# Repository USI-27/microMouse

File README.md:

# MicroMouse  Project

This project implements a micromouse robot using a Raspberry Pi Pico W microcontroller. The robot is designed to solve a maze using the flood fill algorithm, with advanced motion control, wall detection, and a custom-designed PCB.

## Repository Structure

```
MicroMouse/
├── MicroMouse Software/       # Firmware source code
│   ├── Headers/                # Header files (.h)
│   ├── images/                 # README images
│   ├── Cell.cpp
│   ├── IR_Sensors.cpp
│   ├── Int_Vector.cpp
│   ├── Maze_Algorithm.cpp
│   ├── Motion_Planner.cpp
│   ├── Profile.cpp
│   ├── Queue.cpp
│   └── Simple_Run_Micromouse_V1.ino
└── MicroMouse Design Files/   # Hardware design files
    ├── mm3.0/                  # KiCad project (schematic + PCB)
    ├── manufacturing/          # Gerbers, drill files, BOM, pick-and-place
    ├── images/                 # PCB and assembly renders
    ├── schematic.pdf
    └── HARDWARE.md             # Detailed hardware documentation
```

## Hardware Implementation

The image above shows the actual hardware implementation of the micromouse robot, featuring:

- Raspberry Pi Pico W at the center
- Dual motor setup with encoders
- IR sensors for wall detection
- Custom PCB design for component integration
- Compact and efficient layout

Full PCB schematics, KiCad source files, manufacturing (Gerber/BOM) files, and design writeups are available in [`MicroMouse Design Files/`](MicroMouse%20Design%20Files/) — see [`HARDWARE.md`](MicroMouse%20Design%20Files/HARDWARE.md) for a detailed breakdown of the sensor placement and board layout.

## Achievements 🏆

- 🥇 **1st Place** at IIT Roorkee's Annual Tech Fest - Cognizance '25, Micromouse Competition (Prize: ₹1,00,000)
- 🥇 **1st Place** at Delhi Technological University's Annual Tech Fest - Invictus '25, Micromouse Competition
- 🥇 **1st Place** at BITS Pilani's Annual Tech Fest - Apogee '25, Micromouse Competition
- 🥉 **3rd Place** at IIT Jodhpur's Annual Tech Fest - Prometeo '25, Micromouse Competition
- 🥉 **3rd Place** at RGIPT's Annual Tech Fest - Urjotsav '24

## Video Demonstration

Check out the micromouse robot in action: [Watch on YouTube](https://www.youtube.com/watch?v=1PZht_hqyYY)

## Hardware Components

- **Microcontroller**: Raspberry Pi Pico W
- **Motors**: 2 DC motors with encoders
- **Sensors**:
  - IR sensors for wall detection (Left, Right, Front)
  - MPU6050 gyroscope for orientation
  - Encoders for distance measurement
- **Motor Driver**: TB6612FNG dual motor driver

## Project Structure (Software)

The firmware is organized into several key components:

1. **Cell.h/cpp** — Defines the maze cell structure and properties
2. **Int_Vector.h/cpp** — Custom vector implementation for sensor data
3. **IR_Sensors.h/cpp** — Wall detection and sensor reading functionality
4. **Maze_Algorithm.h/cpp** — Flood fill algorithm and maze solving logic
5. **Motion_Planner.h/cpp** — Movement control and motor functions
6. **Profile.h/cpp** — Global configuration and pin definitions
7. **Queue.h/cpp** — Queue implementation for flood fill algorithm

## How It Works

### 1. Initialization (`setup()`)

- Configures serial communication
- Initializes MPU6050 gyroscope
- Sets up encoder pins and interrupts
- Configures motor driver pins
- Sets initial maze walls for the starting position

### 2. Maze Exploration Flow

The robot explores the maze in multiple rounds:

```cpp
for (int round = 1; round <= Exploration_Rounds; round++) {
    searchMode = FIND_CENTRE;  // First find the center
    findGoal();
    searchMode = FIND_START;   // Then return to start
    findGoal();
}
```

### 3. Flood Fill Algorithm

The flood fill algorithm works as follows:

1. Initializes all cells with -1 cost
2. Sets goal cells (center or start) with cost 0
3. Propagates costs to neighboring cells
4. Robot moves to the neighboring cell with lowest cost

### 4. Wall Detection

- Uses IR sensors to detect walls
- Updates maze wall information in real-time
- Maintains wall consistency between adjacent cells

### 5. Movement Control

The robot uses several movement functions:

- `moveForward()`: Move one cell forward
- `turnLeft()`: Turn 90 degrees left
- `turnRight()`: Turn 90 degrees right
- Uses PD (Proportional-Derivative) control for smooth motion
- Gyroscope feedback for accurate turns
- Encoder feedback for distance measurement

### 6. Navigation Logic

**Wall Update:**
```cpp
updateWalls();  // Detect and update wall information
```

**Path Planning:**
```cpp
floodOpenNeighbours();     // Update cell costs
getMinDistanceDirection();  // Choose best direction
```

**Movement:**
```cpp
moveInDirection();  // Execute movement
```

## Key Features

**Adaptive Movement:**
- PD control for straight line motion
- Gyroscope-based rotation control
- Wall following capability

**Intelligent Maze Solving:**
- Flood fill algorithm for path planning
- Multiple exploration rounds
- Efficient center finding and return to start

**Robust Sensor Integration:**
- IR sensor filtering
- Encoder-based distance measurement
- Gyroscope-based orientation tracking

## Configuration

Key parameters can be adjusted in `Profile.h`:

- `MAZE_SIZE`: Size of the maze (default: 8x8)
- `Exploration_Rounds`: Number of exploration rounds
- Sensor thresholds
- Motor control parameters

## Usage

1. Upload the code (`Simple_Run_Micromouse_V1.ino`) to the Raspberry Pi Pico W
2. Place the robot at the start position (0,0)
3. The robot will automatically:
   - Find the path to the center
   - Return to start
   - Repeat for the specified number of rounds
   - Make a final run to the center

## Debugging

- LED indicators for status
- Serial output for debugging
- Button to clear maze walls

## Authors

Built by [USI-27](https://github.com/USI-27) and [paramveer5404](https://github.com/paramveer5404) .

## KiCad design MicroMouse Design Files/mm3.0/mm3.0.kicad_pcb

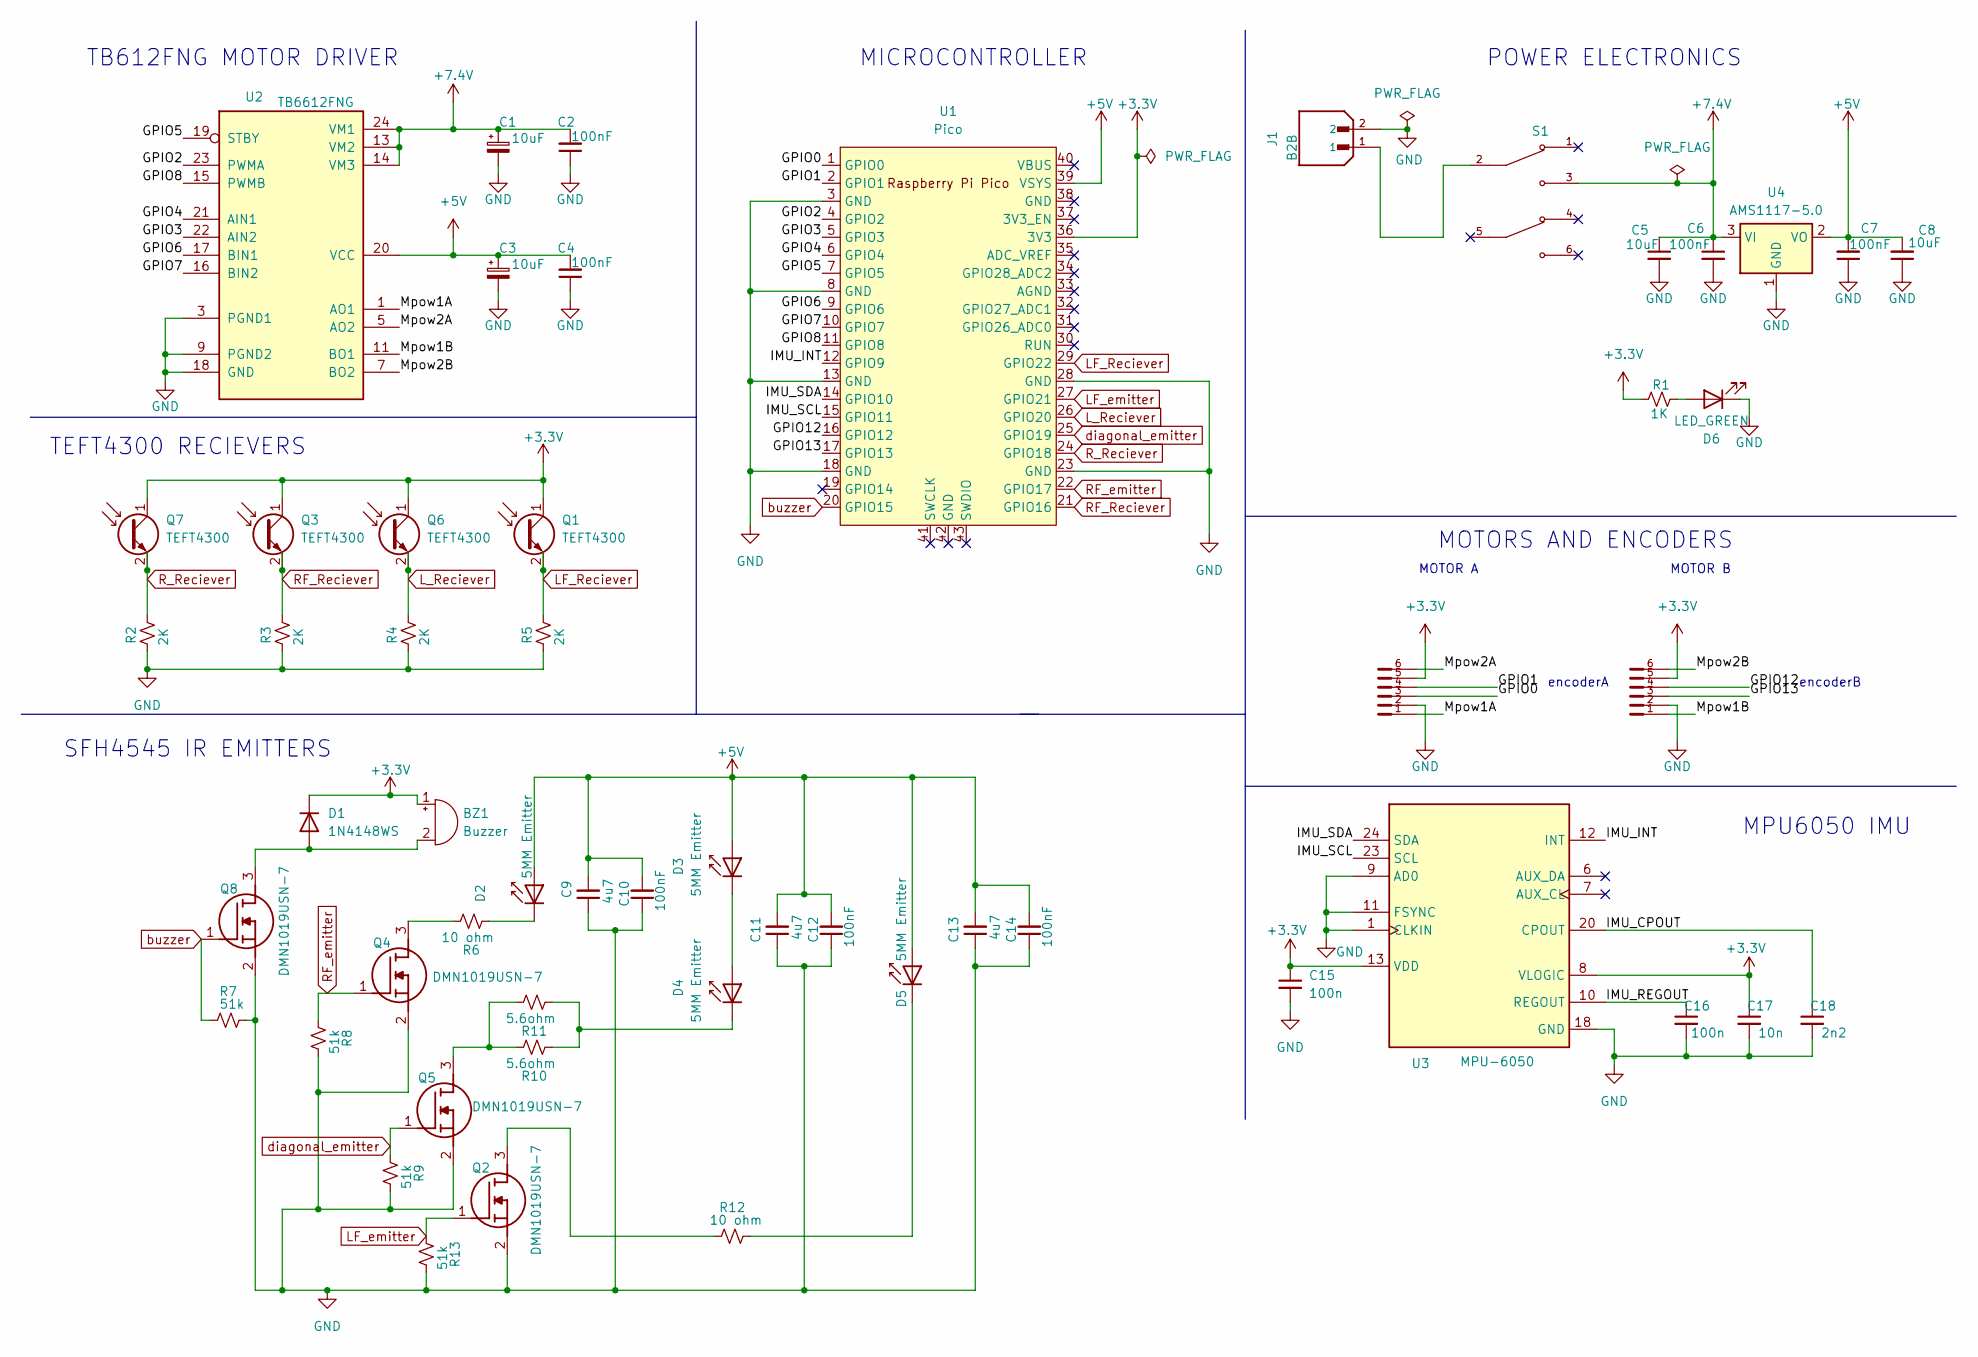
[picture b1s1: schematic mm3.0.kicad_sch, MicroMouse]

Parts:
BZ1: Buzzer; Buzzer_12x9.5RM7.6
C1, C3: 10uF; CP_EIA-3216-10_Kemet-I_Pad1.58x1.35mm_HandSolder; LCSC C7171
C2, C4, C10, C12, C14: 100nF; C_0402_1005Metric_Pad0.74x0.62mm_HandSolder; LCSC C307331
C5, C8: 10uF; C_0805_2012Metric_Pad1.18x1.45mm_HandSolder; LCSC C440198
C6, C7: 100nF; C_0805_2012Metric_Pad1.18x1.45mm_HandSolder; LCSC C495959
C9, C11: 4u7; C_0805_2012Metric_Pad1.18x1.45mm_HandSolder; LCSC C1779
C13: 4u7; C_0805_2012Metric_Pad1.18x1.45mm_HandSolder
C15: 100n; C_0402_1005Metric_Pad0.74x0.62mm_HandSolder; LCSC C307331
C16: 100n; C_0805_2012Metric_Pad1.18x1.45mm_HandSolder; LCSC C495959
C17: 10n; C_0805_2012Metric_Pad1.18x1.45mm_HandSolder; LCSC C1710
C18: 2n2; C_0805_2012Metric_Pad1.18x1.45mm_HandSolder; LCSC C28260
D1: 1N4148WS; D_SOD-323_HandSoldering; LCSC C2128
D2, D3, D4, D5: 5MM Emitter; LED_D5.0mm_IRBlack
D6: LED_GREEN; LED_0805_2012Metric_Pad1.15x1.40mm_HandSolder; LCSC C2297
J1: B2B; JST_XH_B2B-XH-AM_1x02_P2.50mm_Vertical; PARTREV N/A; LCSC C158012
Q1, Q3, Q6, Q7: TEFT4300; LED_D3.0mm_Clear; LCSC C118301
Q2, Q4, Q5, Q8: DMN1019USN-7; SOT95P285X140-3N; Manufacturer_Part_Number DMN1019USN-7; LCSC C145103
R1: 1K; R_0402_1005Metric_Pad0.72x0.64mm_HandSolder; LCSC C11702
R2, R3, R4, R5: 2K; R_1206_3216Metric_Pad1.30x1.75mm_HandSolder; LCSC C17944
R6, R12: 10 ohm; R_0805_2012Metric_Pad1.20x1.40mm_HandSolder; LCSC C136903
R7, R8, R9, R13: 51k; R_2010_5025Metric_Pad1.40x2.65mm_HandSolder; LCSC C20435
R10, R11: 5.6ohm; R_0402_1005Metric_Pad0.72x0.64mm_HandSolder; LCSC C25175
S1: SW_TL2230EEF140; PARTREV E
U1: Pico; RPi_Pico_SMD_TH; LCSC C7203003
U2: TB6612FNG; SSOP-24_5.3x8.2mm_P0.65mm; LCSC C141517
U3: MPU-6050; InvenSense_QFN-24_4x4mm_P0.5mm; LCSC C24112
U4: AMS1117-5.0; SOT-223-3_TabPin2; LCSC C6187
X1, X2: B6B-ZR; DigiKey_Part_Number 455-B6B-ZR-ND

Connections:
+3.3V: BZ1.1 (+), C15.1, C17.1, D1.1 (K), Q1.1 (C), Q3.1 (C), Q6.1 (C), Q7.1 (C), R1.1, U1.36 (3V3), U3.8 (VLOGIC), U3.13 (VDD), X1.5, X2.5
+5V: C3.1, C4.2, C7.2, C8.2, C9.2, C10.2, C11.2, C12.2, C13.2, C14.2, D2.2 (A), D3.2 (A), D5.2 (A), U1.39 (VSYS), U2.20 (VCC), U4.2 (VO)
+7.4V: C1.1, C2.2, C5.1, C6.1, S1.3, U2.13 (VM2), U2.14 (VM3), U2.24 (VM1), U4.3 (VI)
/GPIO0: U1.1 (GPIO0), X1.3
/GPIO1: U1.2 (GPIO1), X1.4
/GPIO2: U1.4 (GPIO2), U2.23 (PWMA)
/GPIO3: U1.5 (GPIO3), U2.22 (AIN2)
/GPIO4: U1.6 (GPIO4), U2.21 (AIN1)
/GPIO5: U1.7 (GPIO5), U2.19 (STBY)
/GPIO6: U1.9 (GPIO6), U2.17 (BIN1)
/GPIO7: U1.10 (GPIO7), U2.16 (BIN2)
/GPIO8: U1.11 (GPIO8), U2.15 (PWMB)
/GPIO12: U1.16 (GPIO12), X2.4
/GPIO13: U1.17 (GPIO13), X2.3
/IMU_CPOUT: C18.1, U3.20 (CPOUT)
/IMU_INT: U1.12 (GPIO9), U3.12 (INT)
/IMU_REGOUT: C16.1, U3.10 (REGOUT)
/IMU_SCL: U1.15 (GPIO11), U3.23 (SCL)
/IMU_SDA: U1.14 (GPIO10), U3.24 (SDA)
/Mpow1A: U2.1 (AO1), U2.2 (AO1), X1.1
/Mpow1B: U2.11 (BO1), U2.12 (BO1), X2.1
/Mpow2A: U2.5 (AO2), U2.6 (AO2), X1.6
/Mpow2B: U2.7 (BO2), U2.8 (BO2), X2.6
GND: C1.2, C2.1, C3.2, C4.1, C5.2, C6.2, C7.1, C8.1, C9.1, C10.1, C11.1, C12.1, C13.1, C14.1, C15.2, C16.2, C17.2, C18.2, D6.1 (K), J1.2, Q2.2 (S), Q4.2 (S), Q5.2 (S), Q8.2 (S), R2.2, R3.2, R4.2, R5.2, R7.2, R8.2, R9.2, R13.2, U1.3 (GND), U1.8 (GND), U1.13 (GND), U1.18 (GND), U1.23 (GND), U1.28 (GND), U2.3 (PGND1), U2.4 (PGND1), U2.9 (PGND2), U2.10 (PGND2), U2.18 (GND), U3.1 (CLKIN), U3.9 (AD0), U3.11 (FSYNC), U3.18 (GND), U4.1 (GND), X1.2, X2.2
LF_Reciever: Q1.2 (E), R5.1, U1.29 (GPIO22)
LF_emitter: Q2.1 (G), R13.1, U1.27 (GPIO21)
L_Reciever: Q6.2 (E), R4.1, U1.26 (GPIO20)
unnamed: BZ1.2 (-), D1.2 (A), Q8.3 (D)
unnamed: D2.1 (K), R6.1
unnamed: D3.1 (K), D4.2 (A)
unnamed: D4.1 (K), R10.1, R11.1
unnamed: D5.1 (K), R12.2
unnamed: D6.2 (A), R1.2
unnamed: J1.1, S1.2
unnamed: Q2.3 (D), R12.1
unnamed: Q4.3 (D), R6.2
unnamed: Q5.3 (D), R10.2, R11.2
RF_Reciever: Q3.2 (E), R3.1, U1.21 (GPIO16)
RF_emitter: Q4.1 (G), R8.1, U1.22 (GPIO17)
R_Reciever: Q7.2 (E), R2.1, U1.24 (GPIO18)
buzzer: Q8.1 (G), R7.1, U1.20 (GPIO15)
diagonal_emitter: Q5.1 (G), R9.1, U1.25 (GPIO19)

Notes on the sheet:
encoderA
MOTORS AND ENCODERS
POWER ELECTRONICS
MICROCONTROLLER
TB612FNG MOTOR DRIVER
SFH4545 IR EMITTERS
MOTOR B
TEFT4300 RECIEVERS
MPU6050 IMU
encoderB
MOTOR A

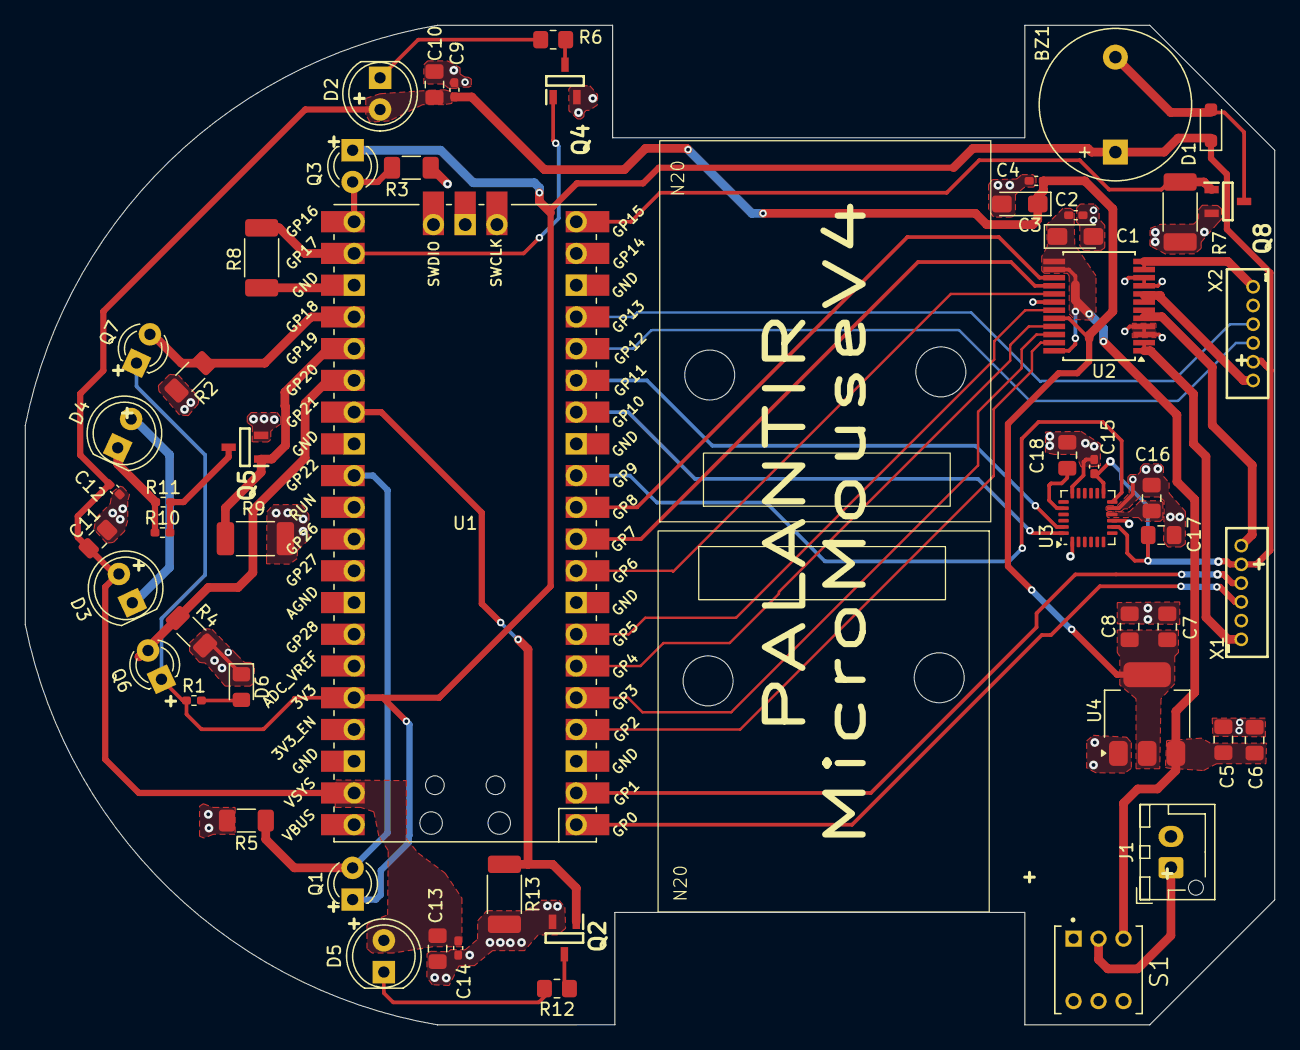
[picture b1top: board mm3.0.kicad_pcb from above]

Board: 2 copper layers, 100.0 x 80.0 mm, 57 parts (1 on the bottom side), 42 nets.

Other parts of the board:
N20, N20#2: N20; N20MotorWithMount
logo: LOGO

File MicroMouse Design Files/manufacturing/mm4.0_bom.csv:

Designator,Comment,Footprint,LCSC
C1,10uF,Capacitor_Tantalum_SMD:CP_EIA-3216-10_Kemet-I_Pad1.58x1.35mm_HandSolder,C7171
C2,100nF,Capacitor_SMD:C_0402_1005Metric_Pad0.74x0.62mm_HandSolder,C307331
C3,10uF,Capacitor_Tantalum_SMD:CP_EIA-3216-10_Kemet-I_Pad1.58x1.35mm_HandSolder,C7171
C4,100nF,Capacitor_SMD:C_0402_1005Metric_Pad0.74x0.62mm_HandSolder,C307331
C5,10uF,Capacitor_SMD:C_0805_2012Metric_Pad1.18x1.45mm_HandSolder,C440198
C6,100nF,Capacitor_SMD:C_0805_2012Metric_Pad1.18x1.45mm_HandSolder,C495959
C7,100nF,Capacitor_SMD:C_0805_2012Metric_Pad1.18x1.45mm_HandSolder,C495959
C8,10uF,Capacitor_SMD:C_0805_2012Metric_Pad1.18x1.45mm_HandSolder,C440198
C9,4u7,Capacitor_SMD:C_0805_2012Metric_Pad1.18x1.45mm_HandSolder,C1779
C10,100nF,Capacitor_SMD:C_0402_1005Metric_Pad0.74x0.62mm_HandSolder,C307331
C11,4u7,Capacitor_SMD:C_0805_2012Metric_Pad1.18x1.45mm_HandSolder,C1779
C12,100nF,Capacitor_SMD:C_0402_1005Metric_Pad0.74x0.62mm_HandSolder,C307331
C13,4u7,Capacitor_SMD:C_0805_2012Metric_Pad1.18x1.45mm_HandSolder,C1779
C14,100nF,Capacitor_SMD:C_0402_1005Metric_Pad0.74x0.62mm_HandSolder,C307331
C15,100n,Capacitor_SMD:C_0402_1005Metric_Pad0.74x0.62mm_HandSolder,C307331
C16,100n,Capacitor_SMD:C_0805_2012Metric_Pad1.18x1.45mm_HandSolder,C495959
C17,10n,Capacitor_SMD:C_0805_2012Metric_Pad1.18x1.45mm_HandSolder,C1710
C18,2n2,Capacitor_SMD:C_0805_2012Metric_Pad1.18x1.45mm_HandSolder,C28260
D1,1N4148WS,Diode_SMD:D_SOD-323_HandSoldering,C2128
D2,5MM Emitter,LED_THT:LED_D5.0mm_IRBlack,
D3,5MM Emitter,LED_THT:LED_D5.0mm_IRBlack,
D4,5MM Emitter,LED_THT:LED_D5.0mm_IRBlack,
D5,5MM Emitter,LED_THT:LED_D5.0mm_IRBlack,
D6,LED_GREEN,LED_SMD:LED_0805_2012Metric_Pad1.15x1.40mm_HandSolder,C2297
J1,B2B,Connector_JST:JST_XH_B2B-XH-AM_1x02_P2.50mm_Vertical,C158012
J2,B2B,Connector_JST:JST_XH_B2B-XH-AM_1x02_P2.50mm_Vertical,C158012
Q1,TEFT4300,LED_THT:LED_D3.0mm_Clear,C118301
Q2,DMN1019USN-7,SPX3819M5-L-5-0:SOT95P285X140-3N,C145103
Q3,TEFT4300,LED_THT:LED_D3.0mm_Clear,C118301
Q4,DMN1019USN-7,SPX3819M5-L-5-0:SOT95P285X140-3N,C145103
Q5,DMN1019USN-7,SPX3819M5-L-5-0:SOT95P285X140-3N,C145103
Q6,TEFT4300,LED_THT:LED_D3.0mm_Clear,C118301
Q7,TEFT4300,LED_THT:LED_D3.0mm_Clear,C118301
Q8,DMN1019USN-7,SPX3819M5-L-5-0:SOT95P285X140-3N,C145103
R1,1K,Resistor_SMD:R_0402_1005Metric_Pad0.72x0.64mm_HandSolder,C11702
R2,2K,Resistor_SMD:R_1206_3216Metric_Pad1.30x1.75mm_HandSolder,C17944
R3,2K,Resistor_SMD:R_1206_3216Metric_Pad1.30x1.75mm_HandSolder,C17944
R4,2K,Resistor_SMD:R_1206_3216Metric_Pad1.30x1.75mm_HandSolder,C17944
R5,2K,Resistor_SMD:R_1206_3216Metric_Pad1.30x1.75mm_HandSolder,C17944
R6,10 ohm,Resistor_SMD:R_0805_2012Metric_Pad1.20x1.40mm_HandSolder,C136903
R7,51k,Resistor_SMD:R_2010_5025Metric_Pad1.40x2.65mm_HandSolder,C20435
R8,51k,Resistor_SMD:R_2010_5025Metric_Pad1.40x2.65mm_HandSolder,C20435
R9,51k,Resistor_SMD:R_2010_5025Metric_Pad1.40x2.65mm_HandSolder,C20435
R10,5.6ohm,Resistor_SMD:R_0402_1005Metric_Pad0.72x0.64mm_HandSolder,C25175
R11,5.6ohm,Resistor_SMD:R_0402_1005Metric_Pad0.72x0.64mm_HandSolder,C25175
R12,10 ohm,Resistor_SMD:R_0805_2012Metric_Pad1.20x1.40mm_HandSolder,C136903
R13,51k,Resistor_SMD:R_2010_5025Metric_Pad1.40x2.65mm_HandSolder,C20435
U1,Pico,MCU_RaspberryPi_and_Boards:RPi_Pico_SMD_TH,C7203003
U2,TB6612FNG,Package_SO:SSOP-24_5.3x8.2mm_P0.65mm,C141517
U3,MPU-6050,Sensor_Motion:InvenSense_QFN-24_4x4mm_P0.5mm,C24112
U4,AMS1117-5.0,Package_TO_SOT_SMD:SOT-223-3_TabPin2,C6187
